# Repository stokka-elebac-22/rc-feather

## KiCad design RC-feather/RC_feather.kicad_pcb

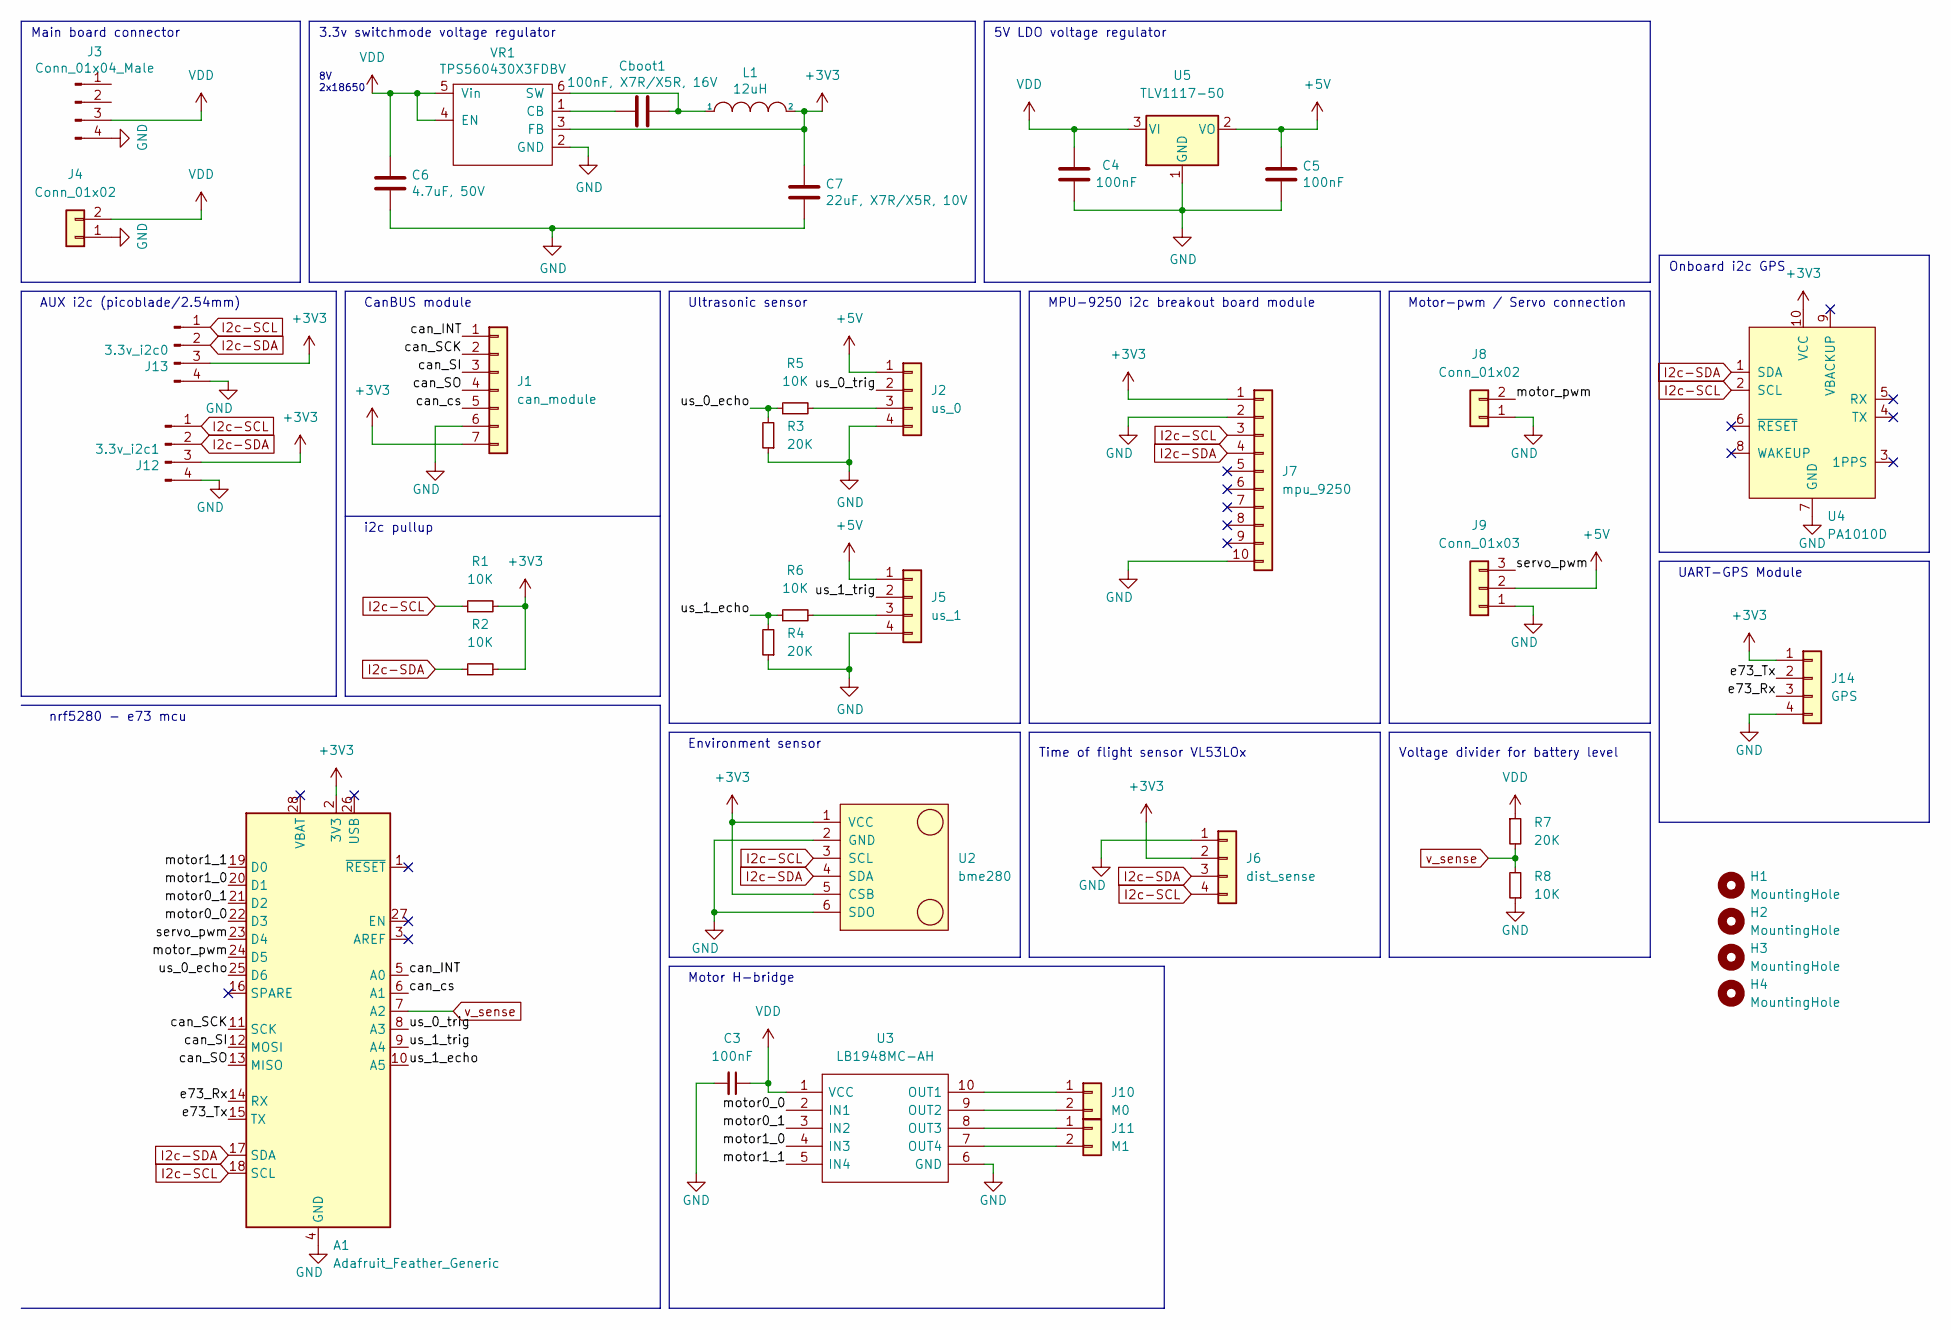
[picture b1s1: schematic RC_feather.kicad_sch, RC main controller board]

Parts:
A1: Adafruit_Feather_Generic; Adafruit_Feather
C3, C4, C5: 100nF; C_1206_3216Metric
C6: 4.7uF, 50V; C_1206_3216Metric
C7: 22uF, X7R/X5R, 10V; C_0805_2012Metric
Cboot1: 100nF, X7R/X5R, 16V; C_0805_2012Metric
H1, H2, H3, H4: MountingHole; MountingHole_3.2mm_M3
J1: can_module; PinSocket_1x07_P2.54mm_Vertical
J2: us_0; PinSocket_1x04_P2.54mm_Vertical
J3: Conn_01x04_Male; JST_XH_S4B-XH-A-1_1x04_P2.50mm_Horizontal-SMD
J4: Conn_01x02; PhoenixContact_MC_1,5_2-G-5.08_1x02_P5.08mm_Horizontal
J5: us_1; PinSocket_1x04_P2.54mm_Vertical
J6: dist_sense; PinSocket_1x04_P2.54mm_Vertical
J7: mpu_9250; PinHeader_1x10_P2.54mm_Vertical
J8: Conn_01x02; PinHeader_1x02_P2.54mm_Vertical
J9: Conn_01x03; PinHeader_1x03_P2.54mm_Vertical
J10: M0; PinHeader_1x02_P2.54mm_Vertical
J11: M1; PinHeader_1x02_P2.54mm_Vertical
J12: 3.3v_i2c1; PinSocket_1x04_P2.54mm_Vertical
J13: 3.3v_i2c0; Molex_PicoBlade_53398-0471_1x04-1MP_P1.25mm_Vertical
J14: GPS; GPS_module
L1: 12uH; IND_SDR0403-120ML
R1, R2, R5, R6, R8: 10K; R_0805_2012Metric_Pad1.20x1.40mm_HandSolder
R3, R4, R7: 20K; R_0805_2012Metric_Pad1.20x1.40mm_HandSolder
U2: bme280; module_bme280
U3: LB1948MC-AH; SOP100P620X155-10N; Mouser Part Number 863-LB1948MC-AH
U4: PA1010D; CDTop_MT3333_PA1010D
U5: TLV1117-50; SOT-223
VR1: TPS560430X3FDBV; SOT-23-6

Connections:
+3V3: A1.2 (3V3), C7.1, J1.7, J6.2, J7.1, J12.3, J13.3, J14.1, L1.2, R1.2, R2.2, U2.1 (VCC), U2.5 (CSB), U4.10 (VCC), VR1.3 (FB)
+5V: C5.1, J2.1, J5.1, J9.2, U5.2 (VO)
/can_INT: A1.5 (A0), J1.1
/can_SCK: A1.11 (SCK), J1.2
/can_SI: A1.12 (MOSI), J1.3
/can_SO: A1.13 (MISO), J1.4
/can_cs: A1.6 (A1), J1.5
/e73_Rx: A1.14 (RX), J14.3
/e73_Tx: A1.15 (TX), J14.2
/motor0_0: A1.22 (D3), U3.2 (IN1)
/motor0_1: A1.21 (D2), U3.3 (IN2)
/motor1_0: A1.20 (D1), U3.4 (IN3)
/motor1_1: A1.19 (D0), U3.5 (IN4)
/motor_pwm: A1.24 (D5), J8.2
/servo_pwm: A1.23 (D4), J9.3
/us_0_echo: A1.25 (D6), R3.2, R5.1
/us_0_trig: A1.8 (A3), J2.2
/us_1_echo: A1.10 (A5), R4.2, R6.1
/us_1_trig: A1.9 (A4), J5.2
GND: A1.4 (GND), C3.2, C4.2, C5.2, C6.2, C7.2, J1.6, J2.4, J3.4, J4.1, J5.4, J6.1, J7.2, J7.10, J8.1, J9.1, J12.4, J13.4, J14.4, R3.1, R4.1, R8.1, U2.2 (GND), U2.6 (SDO), U3.6 (GND), U4.7 (GND), U5.1 (GND), VR1.2 (GND)
I2c-SCL: A1.18 (SCL), J6.4, J7.3, J12.1, J13.1, R1.1, U2.3 (SCL), U4.2 (SCL)
I2c-SDA: A1.17 (SDA), J6.3, J7.4, J12.2, J13.2, R2.1, U2.4 (SDA), U4.1 (SDA)
unnamed: Cboot1.1, L1.1, VR1.6 (SW)
unnamed: Cboot1.2, VR1.1 (CB)
unnamed: J2.3, R5.2
unnamed: J5.3, R6.2
unnamed: J10.1, U3.10 (OUT1)
unnamed: J10.2, U3.9 (OUT2)
unnamed: J11.1, U3.8 (OUT3)
unnamed: J11.2, U3.7 (OUT4)
VDD: C3.1, C4.1, C6.1, J3.3, J4.2, R7.1, U3.1 (VCC), U5.3 (VI), VR1.4 (EN), VR1.5 (Vin)
v_sense: A1.7 (A2), R7.2, R8.2

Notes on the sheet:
Motor-pwm / Servo connection
8V 2x18650
Motor H-bridge
Main board connector
AUX i2c (picoblade/2.54mm)
Time of flight sensor VL53LOx
Voltage divider for battery level
i2c pullup
Onboard i2c GPS
3.3v switchmode voltage regulator
UART-GPS Module
MPU-9250 i2c breakout board module
Environment sensor
CanBUS module
Ultrasonic sensor
nrf5280 - e73 mcu
5V LDO voltage regulator

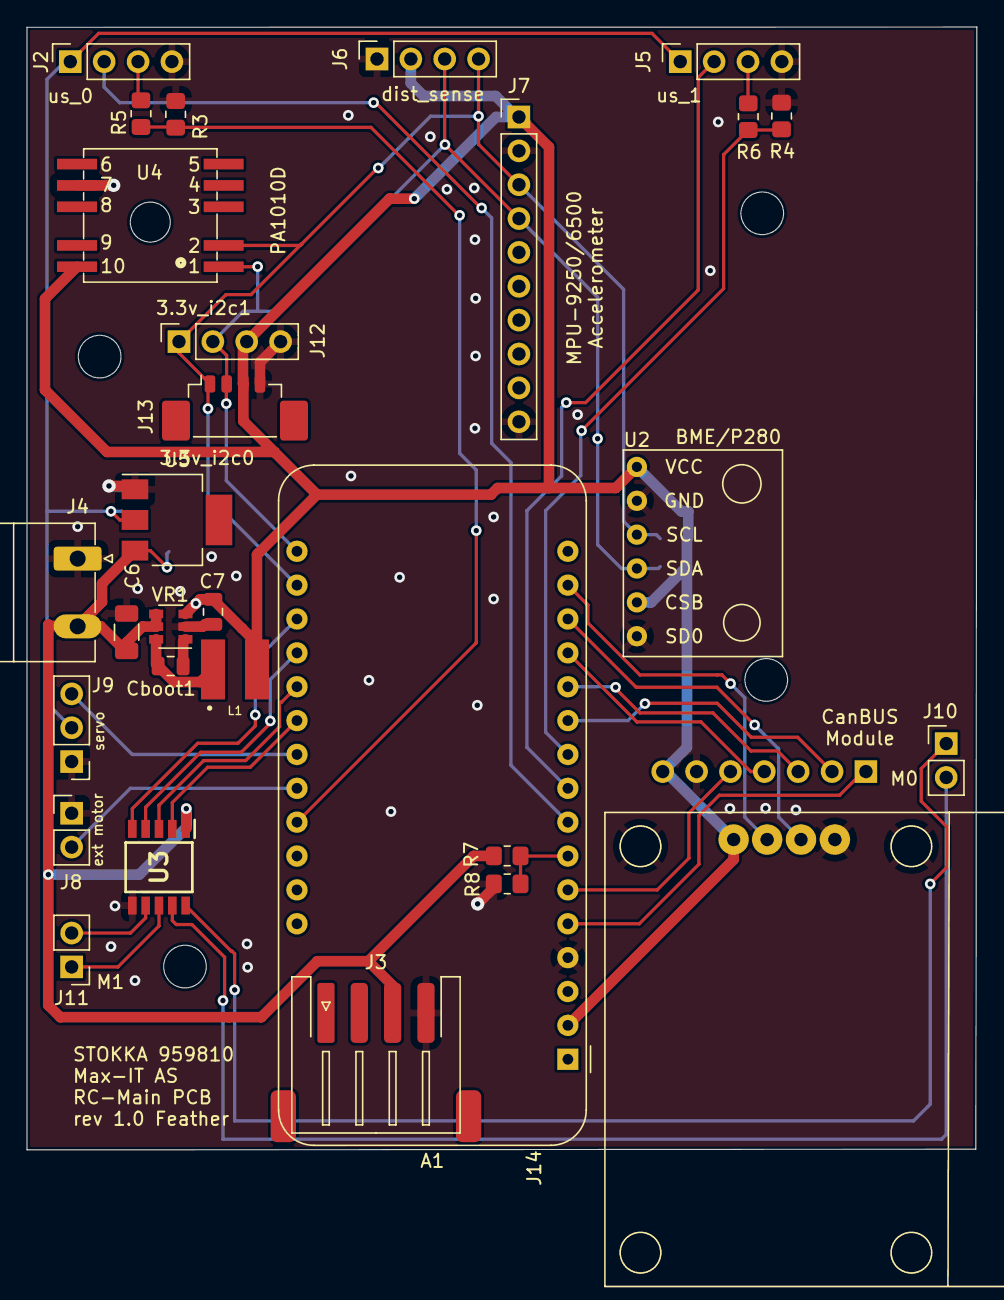
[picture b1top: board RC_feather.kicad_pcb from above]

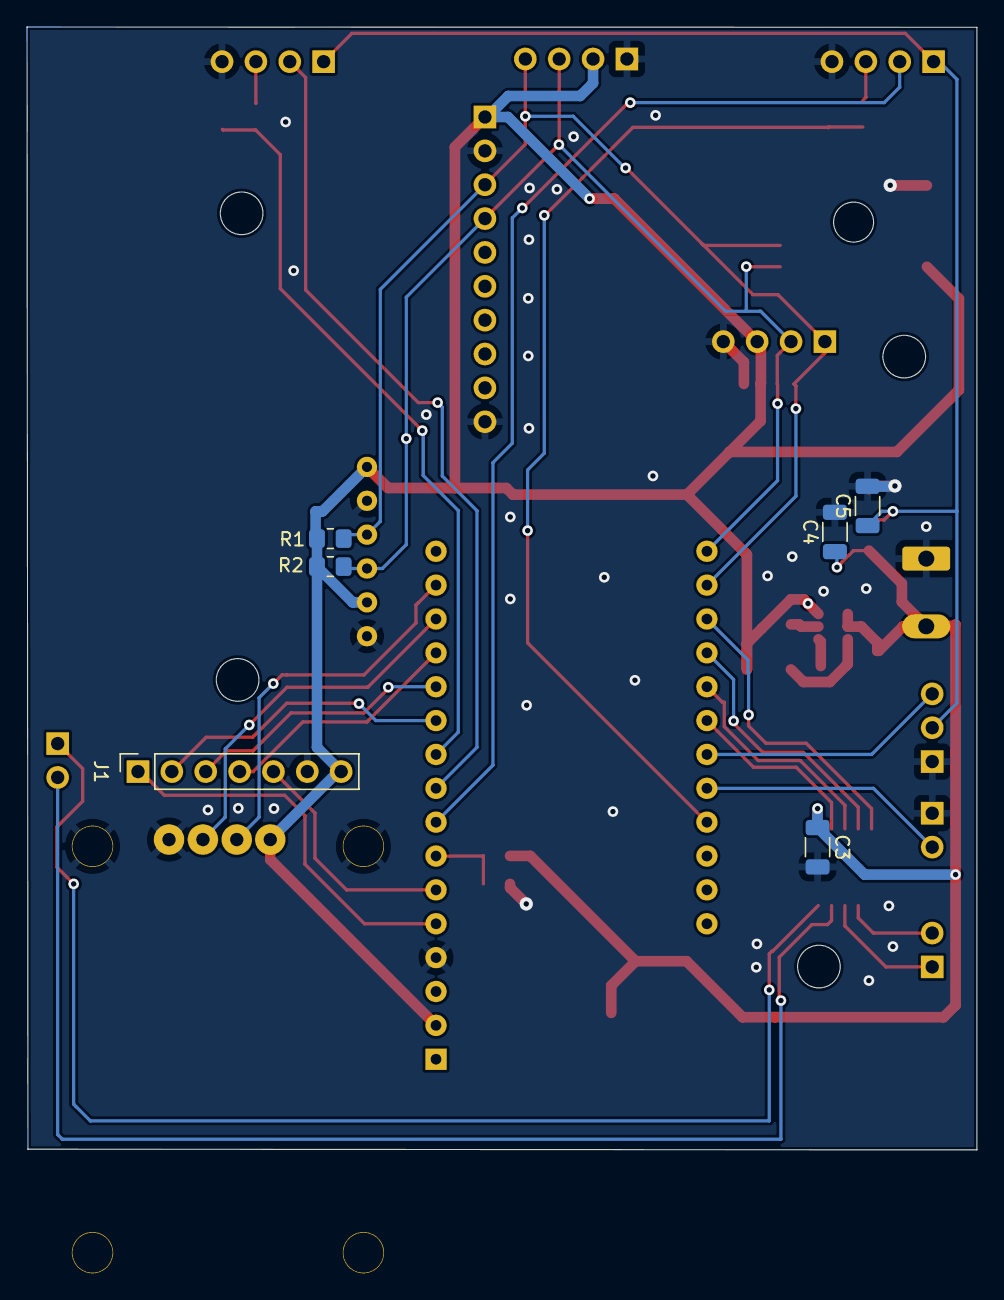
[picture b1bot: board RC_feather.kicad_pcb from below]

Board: 2 copper layers, 71.2 x 84.2 mm, 39 parts (6 on the bottom side), 32 nets.

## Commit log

2022-11-30 initial commit
    Rev 1.0
2022-11-30 kicost test
2022-11-30 netlist output
2022-11-30 preflight update_xml: true
